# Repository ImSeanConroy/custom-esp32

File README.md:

# Custom ESP32

Complete design files for an ESP32 microcontroller-based board, created using KiCad

## License

This project is Distributed under the MIT License - see the [LICENSE](LICENSE) file for information.

## Support

If you are having problems, please let me know by [raising a new issue](https://github.com/ImSeanConroy/custom-esp32/issues/new/choose).

## Acknowledgments

A special thanks to the creators of these invaluable resources that helped guide this project:

- [How to Design a Custom ESP32 PCB](https://thehardwareacademy.com/courses/how-to-design-esp32-pcb/): Learn how to design a custom PCB using the Espressif ESP32-S3 WiFi/Bluetooth wireless microcontroller module.

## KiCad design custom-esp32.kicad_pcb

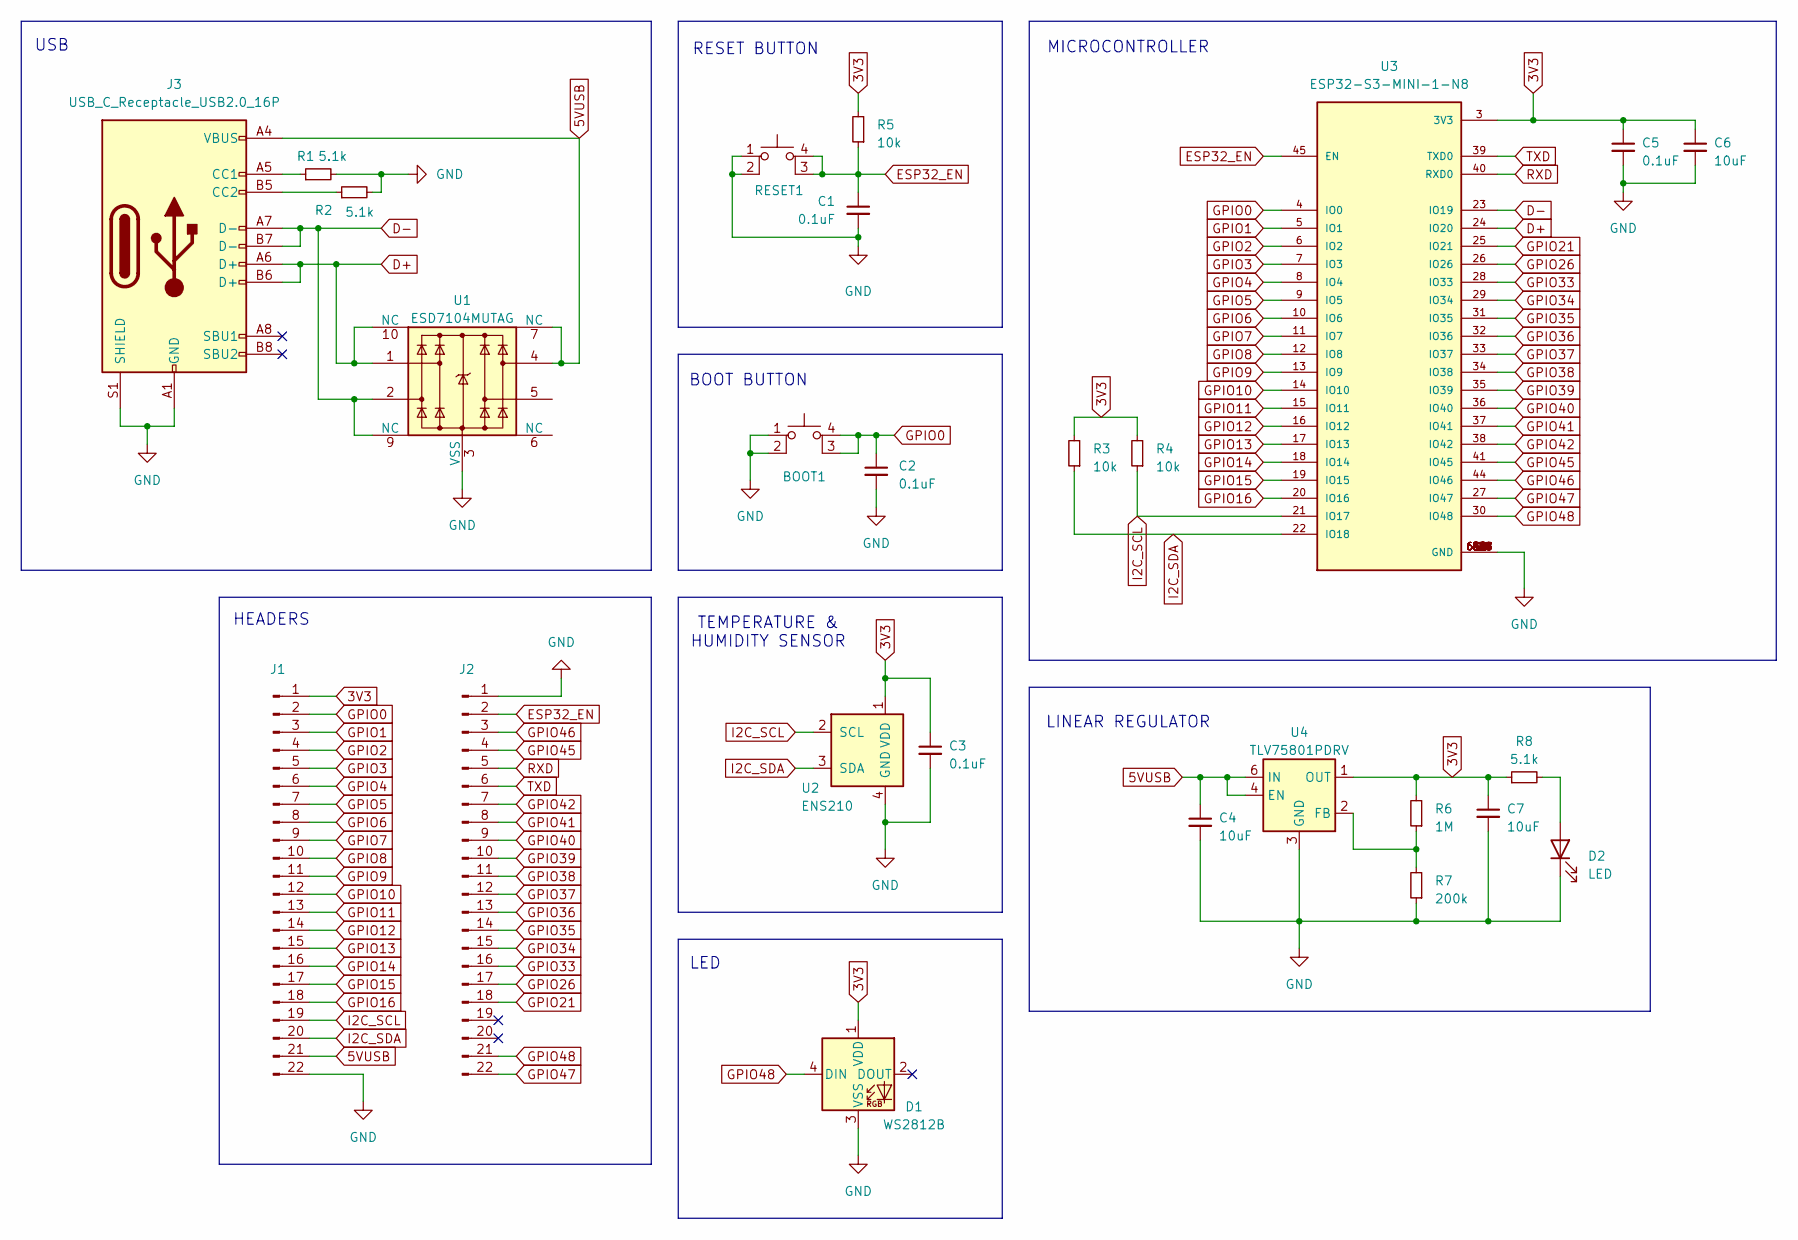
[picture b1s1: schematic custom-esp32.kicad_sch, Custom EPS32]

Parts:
BOOT1: SW_SPST_PTS810
C1, C2, C3, C5: 0.1uF; C_0603_1608Metric
C4, C6, C7: 10uF; C_0603_1608Metric
D1: WS2812B; LED_WS2812B_PLCC4_5.0x5.0mm_P3.2mm
D2: LED; LED_0603_1608Metric
J1, J2: PinHeader_1x22_P2.54mm_Vertical
J3: USB_C_Receptacle_USB2.0_16P; USB_C_Receptacle_GCT_USB4105-xx-A_16P_TopMnt_Horizontal
R1, R2, R8: 5.1k; R_0603_1608Metric
R3, R4, R5: 10k; R_0603_1608Metric
R6: 1M; R_0603_1608Metric
R7: 200k; R_0603_1608Metric
RESET1: SW_SPST_PTS810
U1: ESD7104MUTAG; Diodes_UDFN-10_1.0x2.5mm_P0.5mm
U2: ENS210; AMS_QFN-4-1EP_2x2mm_P0.95mm_EP0.7x1.6mm
U3: ESP32-S3-MINI-1-N8; XCVR_ESP32-S3-MINI-1-N8; PARTREV v0.6
U4: TLV75801PDRV; WSON-6-1EP_2x2mm_P0.65mm_EP1x1.6mm

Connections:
3V3: C3.1, C5.1, C6.1, C7.1, D1.1 (VDD), J1.1, R3.2, R4.2, R5.2, R6.2, R8.1, U2.1 (VDD), U3.3 (3V3), U4.1 (OUT)
5VUSB: C4.1, J1.21, J3.A4 (VBUS), J3.A9 (VBUS), J3.B4 (VBUS), J3.B9 (VBUS), U1.4, U1.7 (NC), U4.4 (EN), U4.6 (IN)
D+: J3.A6 (D+), J3.B6 (D+), U1.1, U1.10 (NC), U3.24 (IO20)
D-: J3.A7 (D-), J3.B7 (D-), U1.2, U1.9 (NC), U3.23 (IO19)
ESP32_EN: C1.1, J2.2, R5.1, RESET1.3 (K), RESET1.4 (A), U3.45 (EN)
GND: BOOT1.1, BOOT1.2, C1.2, C2.2, C3.2, C4.2, C5.2, C6.2, C7.2, D1.3 (VSS), D2.1 (K), J1.22, J2.1, J3.A1 (GND), J3.A12 (GND), J3.B1 (GND), J3.B12 (GND), J3.S1 (SHIELD), R1.2, R2.2, R7.1, RESET1.1, RESET1.2, U1.3 (VSS), U1.8 (VSS), U2.4 (GND), U2.5 (GND), U3.1 (GND), U3.2 (GND), U3.42 (GND), U3.43 (GND), U3.46 (GND), U3.47 (GND), U3.48 (GND), U3.49 (GND), U3.50 (GND), U3.51 (GND), U3.52 (GND), U3.53 (GND), U3.54 (GND), U3.55 (GND), U3.56 (GND), U3.57 (GND), U3.58 (GND), U3.59 (GND), U3.60 (GND), U3.61 (GND), U3.61_1 (GND), U3.61_2 (GND), U3.61_3 (GND), U3.61_4 (GND), U3.61_5 (GND), U3.61_6 (GND), U3.61_7 (GND), U3.61_8 (GND), U3.62 (GND), U3.63 (GND), U3.64 (GND), U3.65 (GND), U4.3 (GND), U4.7 (GND)
GPIO0: BOOT1.3 (K), BOOT1.4 (A), C2.1, J1.2, U3.4 (IO0)
GPIO1: J1.3, U3.5 (IO1)
GPIO2: J1.4, U3.6 (IO2)
GPIO3: J1.5, U3.7 (IO3)
GPIO4: J1.6, U3.8 (IO4)
GPIO5: J1.7, U3.9 (IO5)
GPIO6: J1.8, U3.10 (IO6)
GPIO7: J1.9, U3.11 (IO7)
GPIO8: J1.10, U3.12 (IO8)
GPIO9: J1.11, U3.13 (IO9)
GPIO10: J1.12, U3.14 (IO10)
GPIO11: J1.13, U3.15 (IO11)
GPIO12: J1.14, U3.16 (IO12)
GPIO13: J1.15, U3.17 (IO13)
GPIO14: J1.16, U3.18 (IO14)
GPIO15: J1.17, U3.19 (IO15)
GPIO16: J1.18, U3.20 (IO16)
GPIO21: J2.18, U3.25 (IO21)
GPIO26: J2.17, U3.26 (IO26)
GPIO33: J2.16, U3.28 (IO33)
GPIO34: J2.15, U3.29 (IO34)
GPIO35: J2.14, U3.31 (IO35)
GPIO36: J2.13, U3.32 (IO36)
GPIO37: J2.12, U3.33 (IO37)
GPIO38: J2.11, U3.34 (IO38)
GPIO39: J2.10, U3.35 (IO39)
GPIO40: J2.9, U3.36 (IO40)
GPIO41: J2.8, U3.37 (IO41)
GPIO42: J2.7, U3.38 (IO42)
GPIO45: J2.4, U3.41 (IO45)
GPIO46: J2.3, U3.44 (IO46)
GPIO47: J2.22, U3.27 (IO47)
GPIO48: D1.4 (DIN), J2.21, U3.30 (IO48)
I2C_SCL: J1.19, R4.1, U2.2 (SCL), U3.21 (IO17)
I2C_SDA: J1.20, R3.1, U2.3 (SDA), U3.22 (IO18)
unnamed: D2.2 (A), R8.2
unnamed: J3.A5 (CC1), R1.1
unnamed: J3.B5 (CC2), R2.1
unnamed: R6.1, R7.2, U4.2 (FB)
RXD: J2.5, U3.40 (RXD0)
TXD: J2.6, U3.39 (TXD0)

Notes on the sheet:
RESET BUTTON
MICROCONTROLLER
LINEAR REGULATOR
LED
BOOT BUTTON
TEMPERATURE & HUMIDITY SENSOR
HEADERS
USB

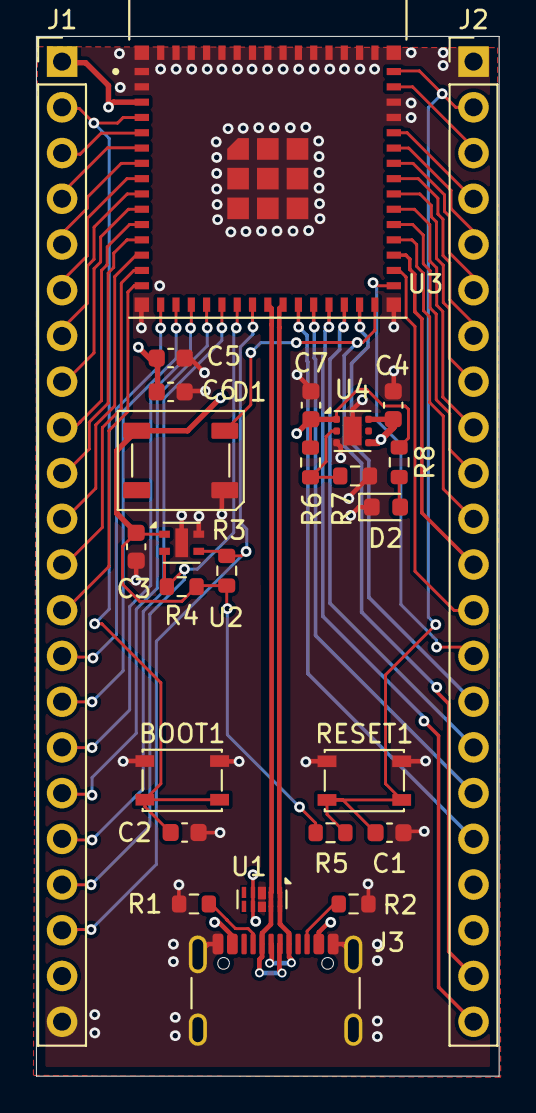
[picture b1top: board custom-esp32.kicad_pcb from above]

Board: 4 copper layers, 25.7 x 57.8 mm, 26 parts (0 on the bottom side), 47 nets.

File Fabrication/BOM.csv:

Designator,Qty,JLPCB Part #,Value,Footprint
U3,1,ESP32-S3-MINI-1-N8,-,ESP32-S3-MINI-1-N8:XCVR_ESP32-S3-MINI-1-N8
U1,1,ESD7104MUTAG,-,Package_DFN_QFN:Diodes_UDFN-10_1.0x2.5mm_P0.5mm
U4,1,TLV75801PDRVR,-,Package_SON:WSON-6-1EP_2x2mm_P0.65mm_EP1x1.6mm
U2,1,ENS210-LQFM,-,Package_DFN_QFN:AMS_QFN-4-1EP_2x2mm_P0.95mm_EP0.7x1.6mm
"BOOT1, RESET1",2,PTS810 SJK 250 SMTR LFS,-,Button_Switch_SMD:SW_SPST_PTS810
J3,1,USB4105-GF-A,-,Connector_USB:USB_C_Receptacle_GCT_USB4105-xx-A_16P_TopMnt_Horizontal
D1,1,COM-16347,-,LED_SMD:LED_WS2812B_PLCC4_5.0x5.0mm_P3.2mm
D2,1,150060RS75000,-,LED_SMD:LED_0603_1608Metric
"J1, J2",2,61302211121,-,Connector_PinHeader_2.54mm:PinHeader_1x22_P2.54mm_Vertical
"C1, C2, C3, C5",4,CC0603KRX7R7BB104,0.1uF,Capacitor_SMD:C_0603_1608Metric
"C4, C6, C7",3,CL10A106MQ8NNNC,10uF,Capacitor_SMD:C_0603_1608Metric
"R1, R2, R8",3,RC0603FR-075K1L,5.1k,Resistor_SMD:R_0603_1608Metric
"R3, R4, R5",3,RC0603FR-0710KL,10k,Resistor_SMD:R_0603_1608Metric
R6,1,RT0603BRD071ML,1M,Resistor_SMD:R_0603_1608Metric
R7,1,RC0603FR-07200KL,200k,Resistor_SMD:R_0603_1608Metric

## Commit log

2024-11-16 Setup kicad project
2024-11-16 Create schematic
2025-02-02 Update schematic
2025-02-03 Add initial pcb layout
2025-02-04 Connect remaining components in pcb layout
2025-02-05 Add missing 3d models and resolve design issues
2025-02-05 Add fabrication files
